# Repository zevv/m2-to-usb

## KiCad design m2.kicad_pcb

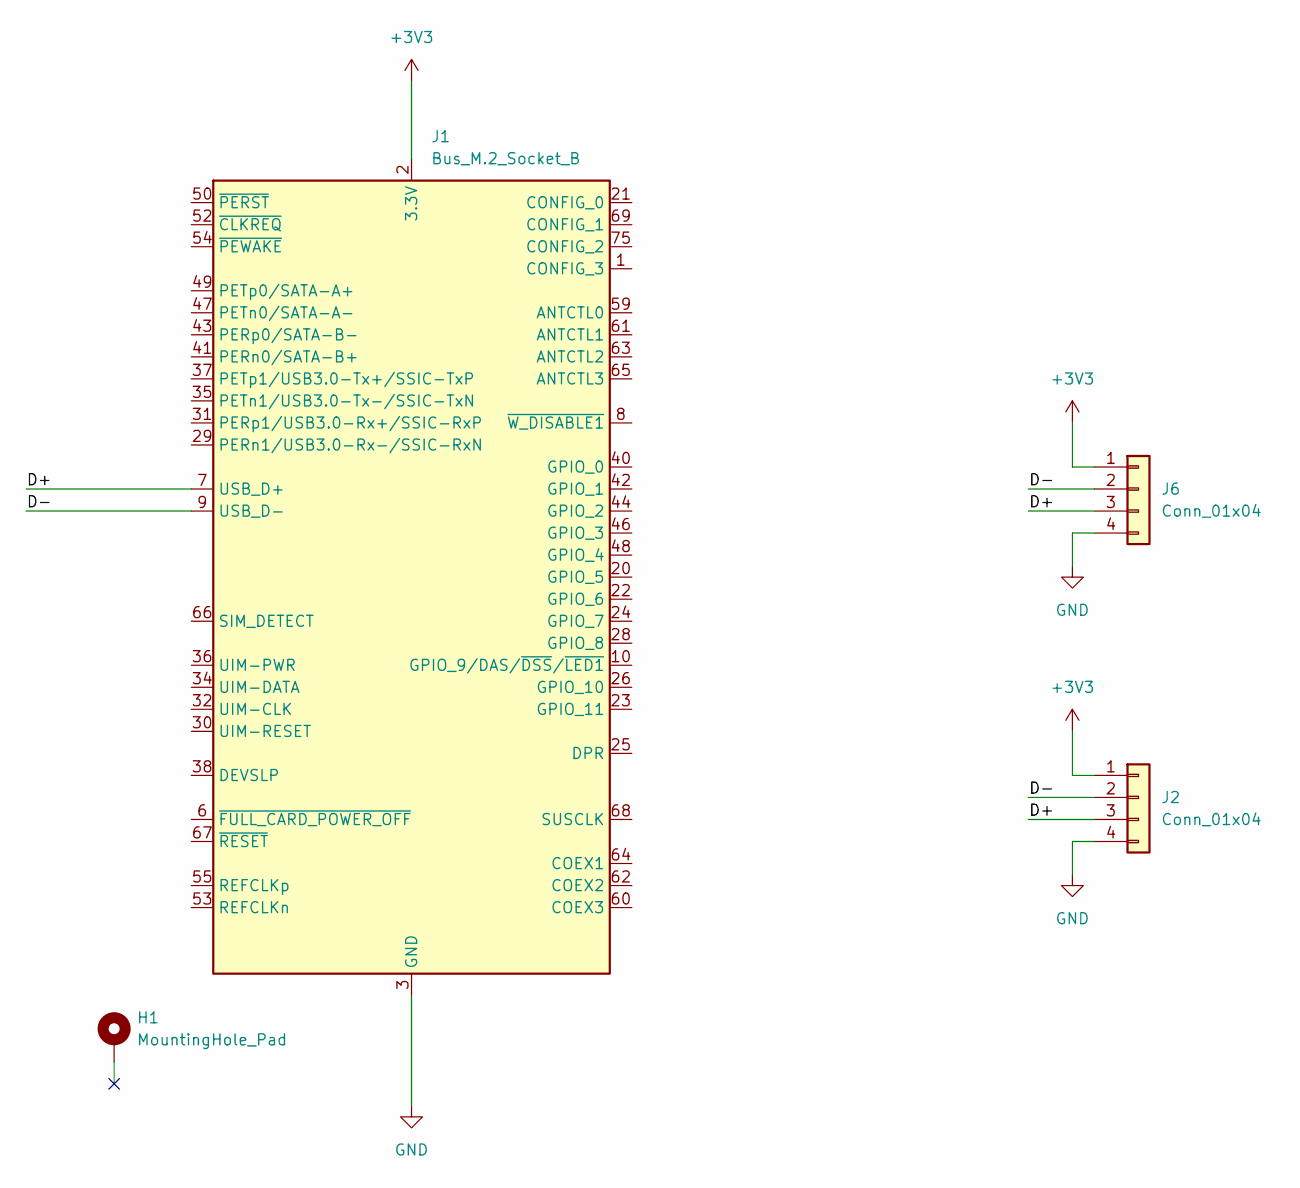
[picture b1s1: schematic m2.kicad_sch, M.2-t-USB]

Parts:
H1: MountingHole_Pad
J1: Bus_M.2_Socket_B; NGFF_B
J2, J6: Conn_01x04; USB

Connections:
+3V3: J1.2 (3.3V), J1.4 (3.3V), J1.70 (3.3V), J1.72 (3.3V), J1.74 (3.3V), J2.1, J6.1
/D+: J1.7 (USB_D+), J2.3, J6.3
/D-: J1.9 (USB_D-), J2.2, J6.2
GND: H1.1, J1.3 (GND), J1.5 (GND), J1.11 (GND), J1.27 (GND), J1.33 (GND), J1.39 (GND), J1.45 (GND), J1.51 (GND), J1.57 (GND), J1.71 (GND), J1.73 (GND), J2.4, J6.4

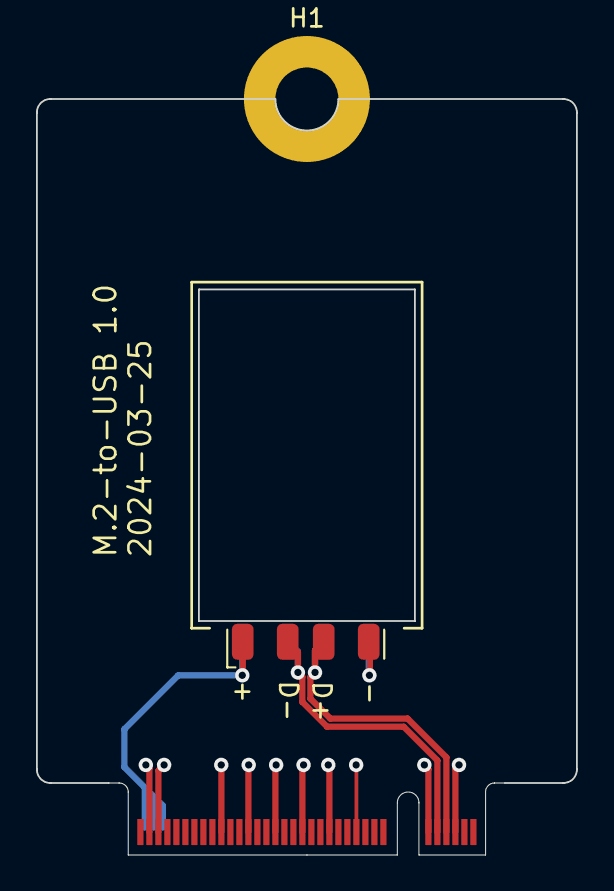
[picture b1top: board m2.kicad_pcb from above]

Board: 2 copper layers, 30.0 x 42.0 mm, 4 parts (1 on the bottom side), 4 nets.

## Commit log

2023-11-09 checkin
2024-03-25 stuff
2024-03-25 cleanups
